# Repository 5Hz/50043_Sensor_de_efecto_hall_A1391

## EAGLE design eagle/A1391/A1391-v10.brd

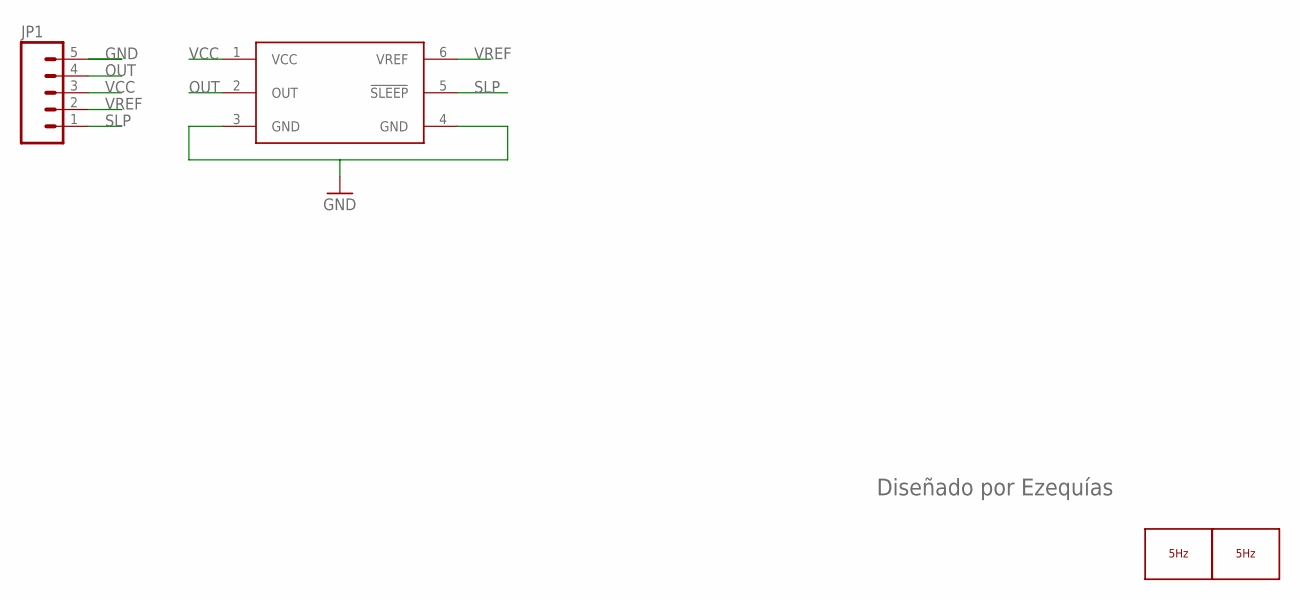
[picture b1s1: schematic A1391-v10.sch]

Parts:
JP1: M05PTH; 1X05
LOGO1: LOGO_5HZ_CIRC_4MM; 5HZ_LOGO_CIRC_4MM
LOGO2: LOGO_5HZ_MAIN_10MM; 5HZ_LOGO_MAIN_10MM
U$1: A1391DFN; DFN-6

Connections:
GND: JP1.5, U$1.3 (GND), U$1.4 (GND)
OUT: JP1.4, U$1.2 (OUT)
SLP: JP1.1, U$1.5 (!SLEEP)
VCC: JP1.3, U$1.1 (VCC)
VREF: JP1.2, U$1.6 (VREF)

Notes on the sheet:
Diseñado por Ezequías

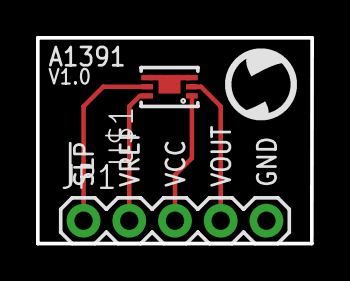
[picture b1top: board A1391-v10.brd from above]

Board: 2 copper layers, 15.2 x 11.4 mm, 4 parts (1 on the bottom side), 5 nets.

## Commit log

2014-01-10 creación
